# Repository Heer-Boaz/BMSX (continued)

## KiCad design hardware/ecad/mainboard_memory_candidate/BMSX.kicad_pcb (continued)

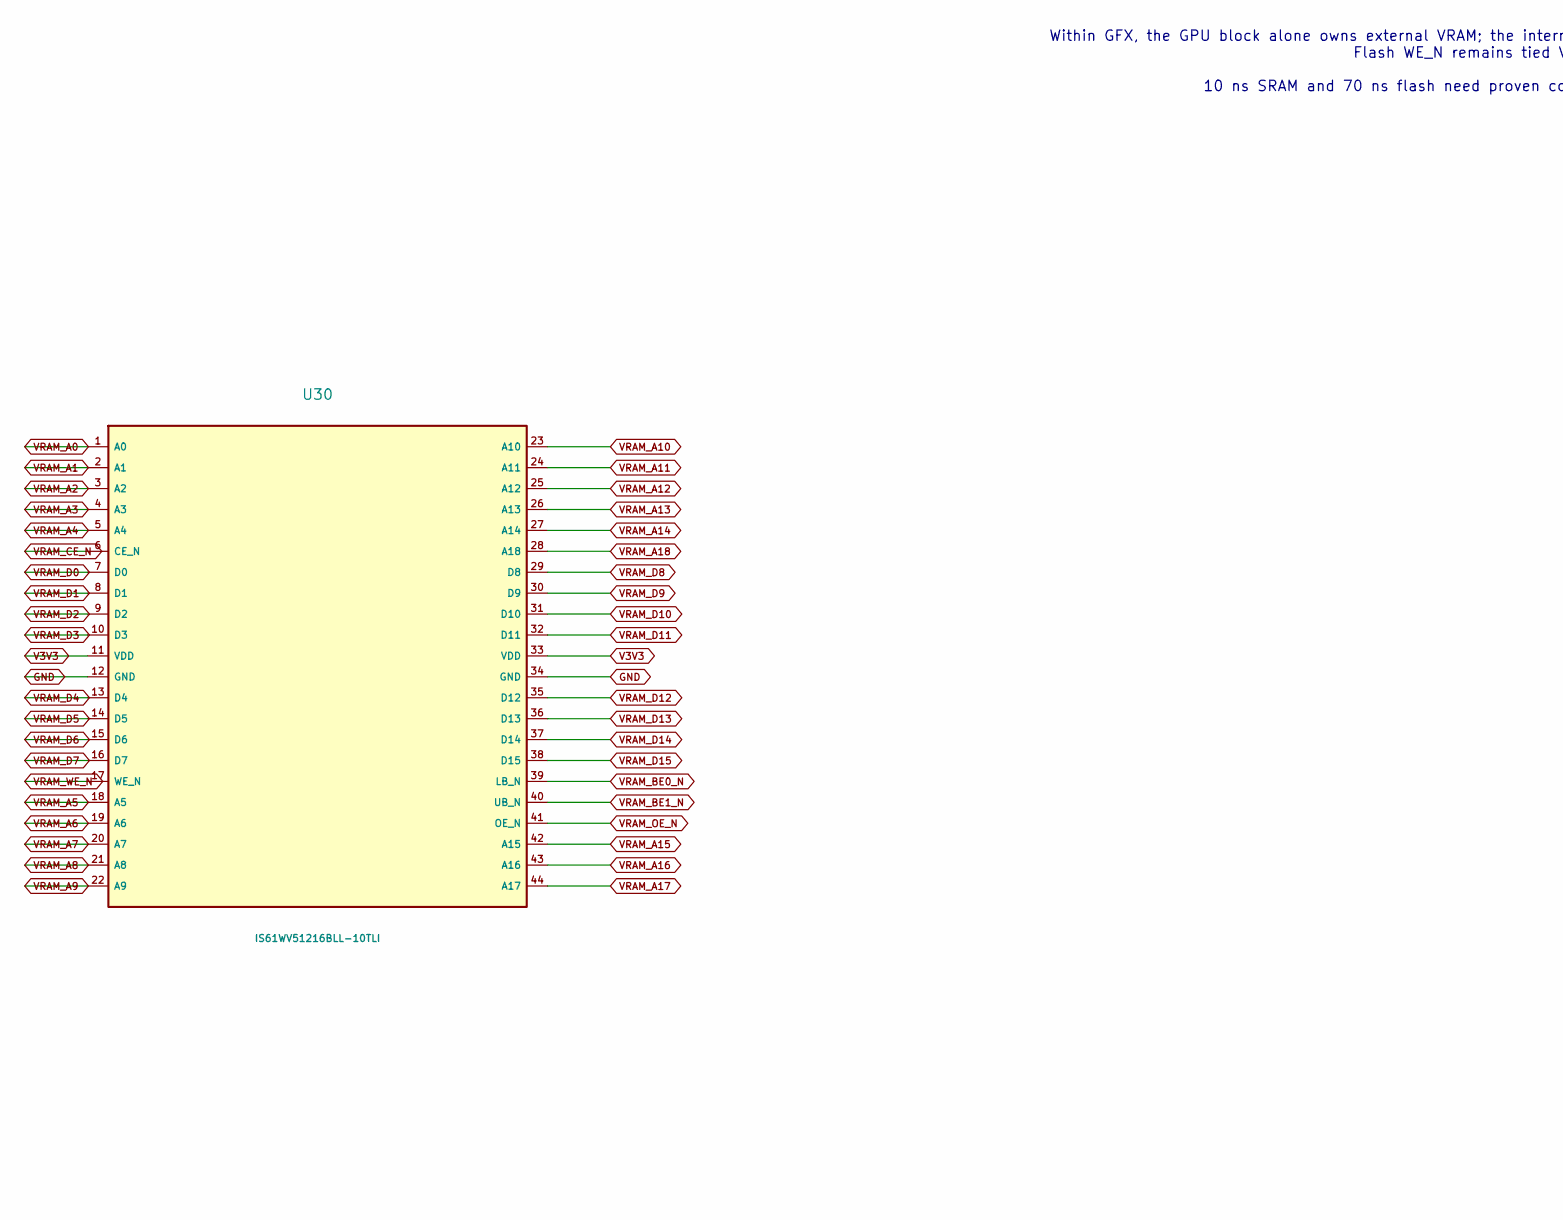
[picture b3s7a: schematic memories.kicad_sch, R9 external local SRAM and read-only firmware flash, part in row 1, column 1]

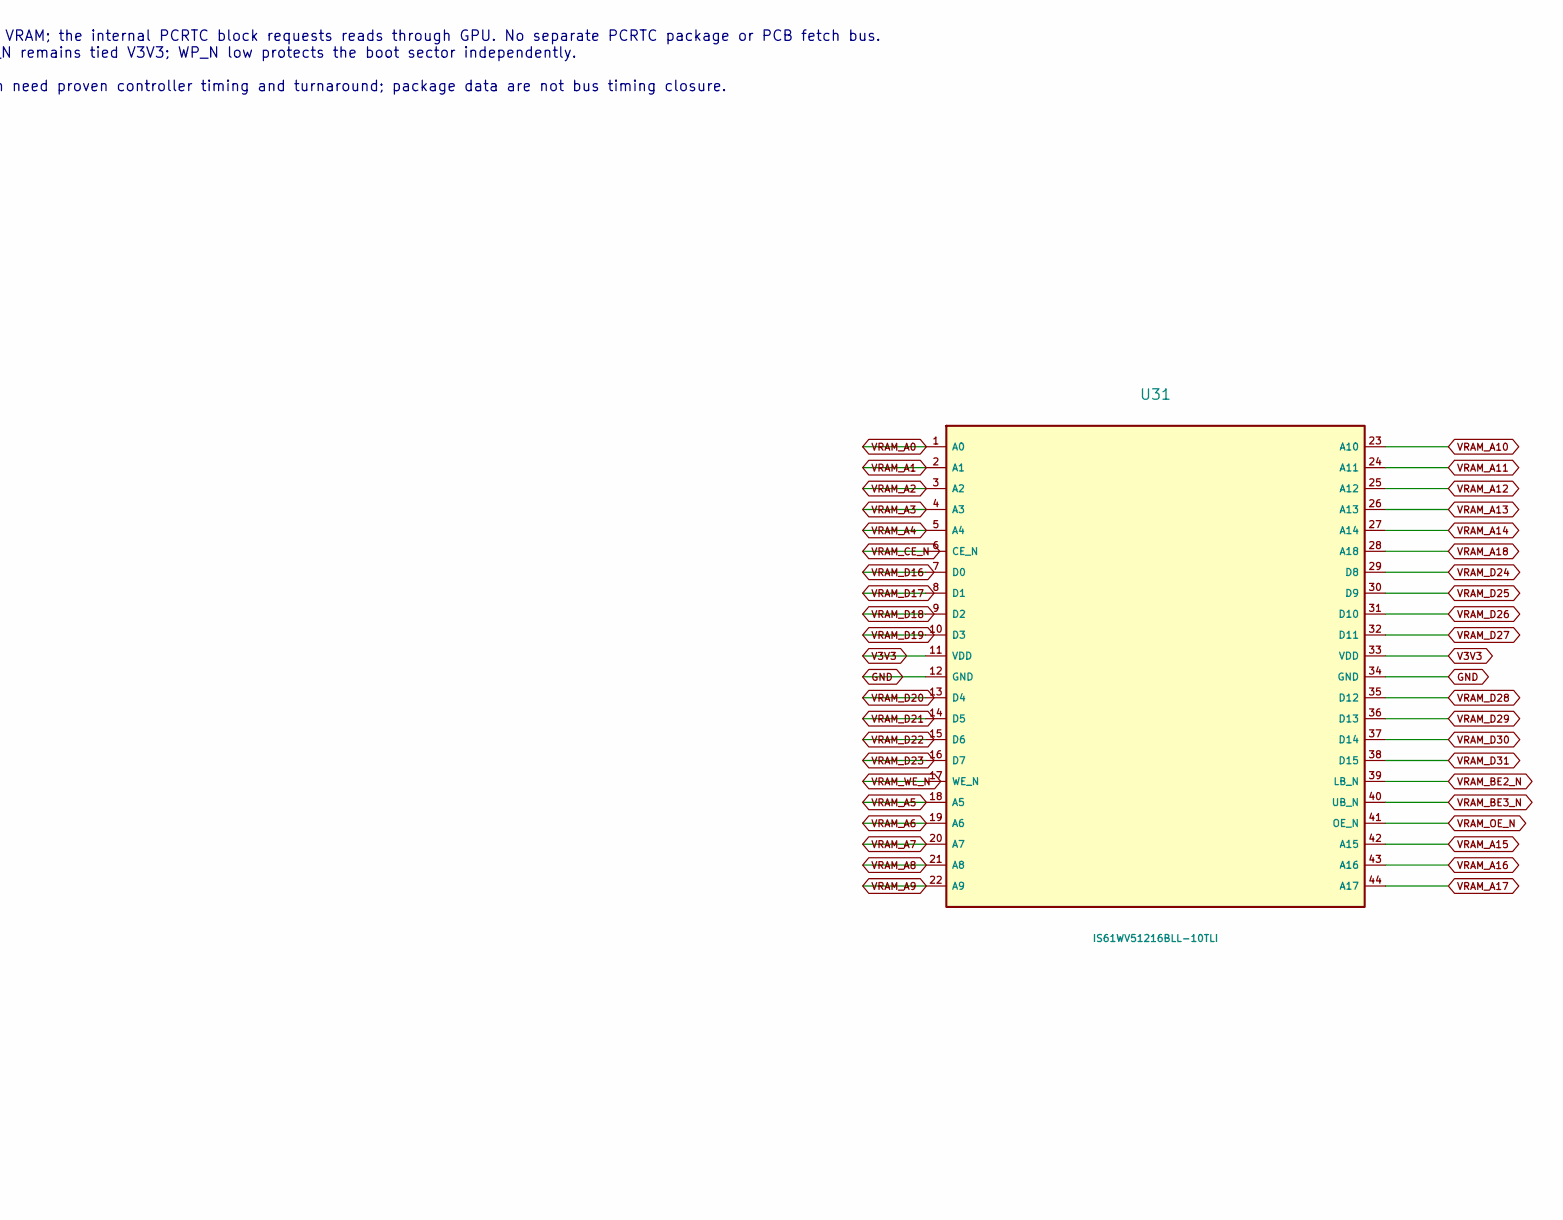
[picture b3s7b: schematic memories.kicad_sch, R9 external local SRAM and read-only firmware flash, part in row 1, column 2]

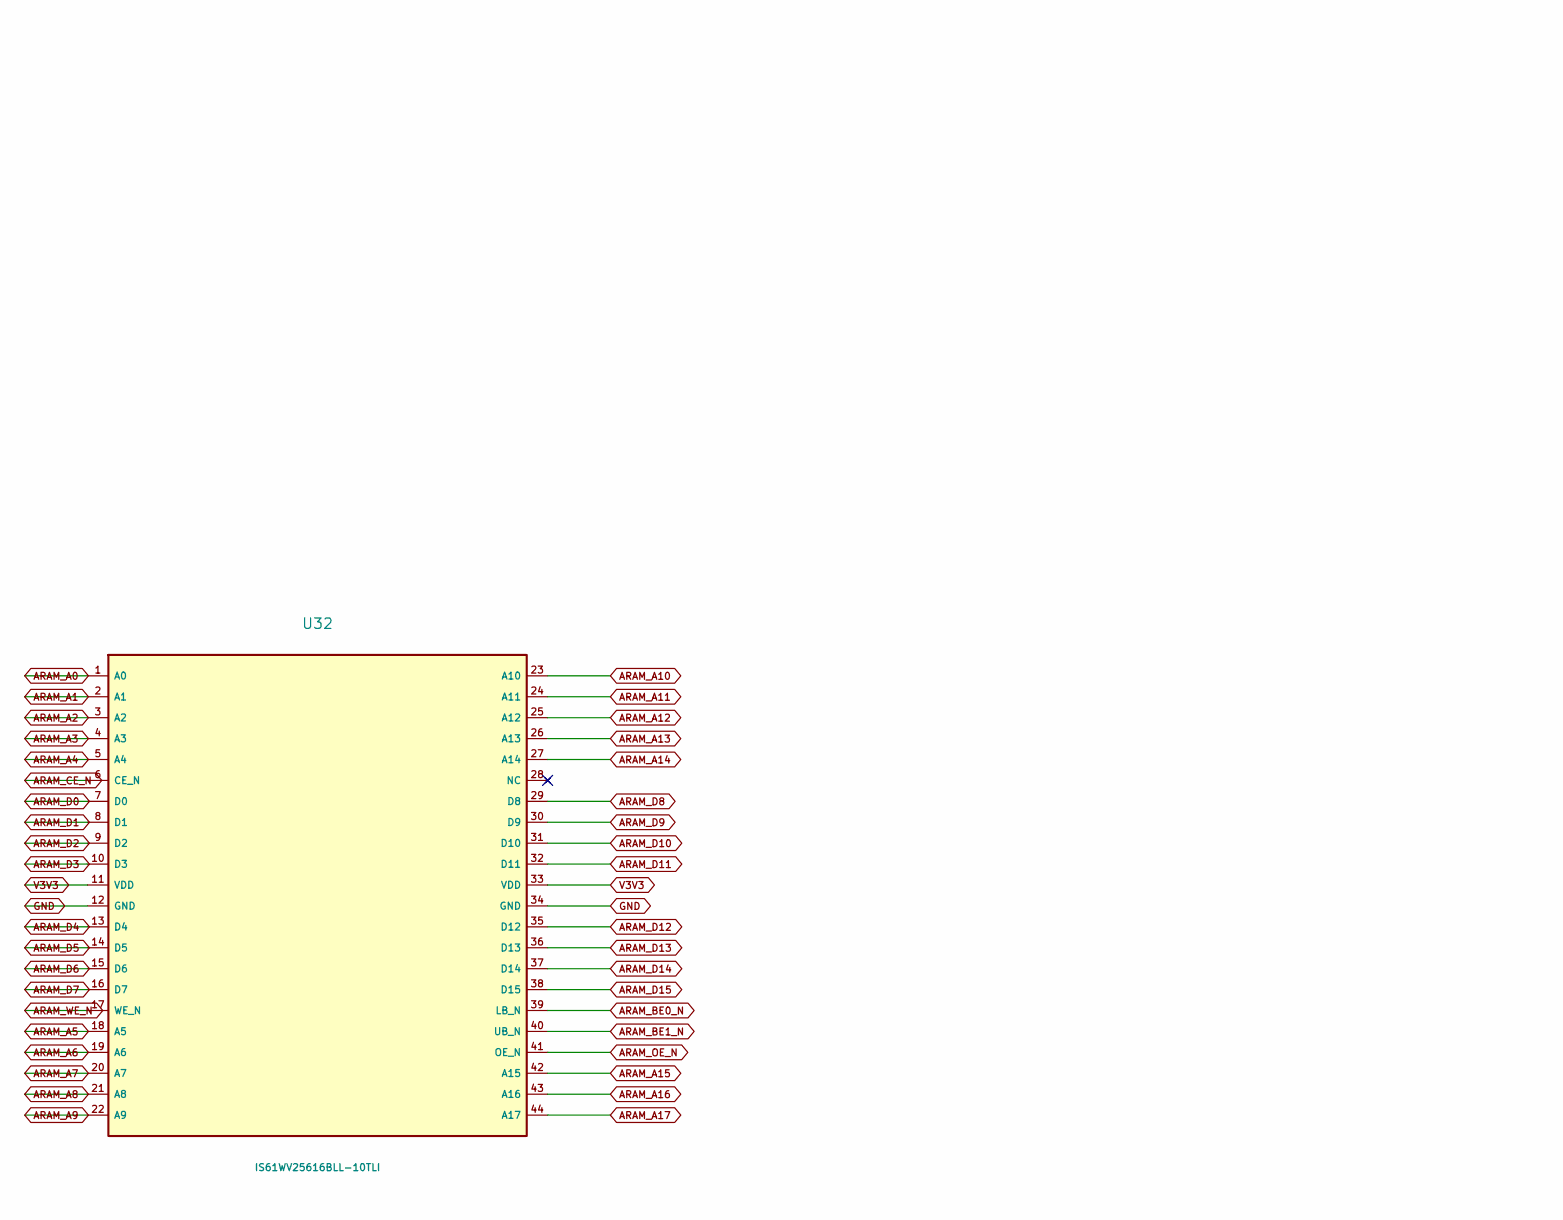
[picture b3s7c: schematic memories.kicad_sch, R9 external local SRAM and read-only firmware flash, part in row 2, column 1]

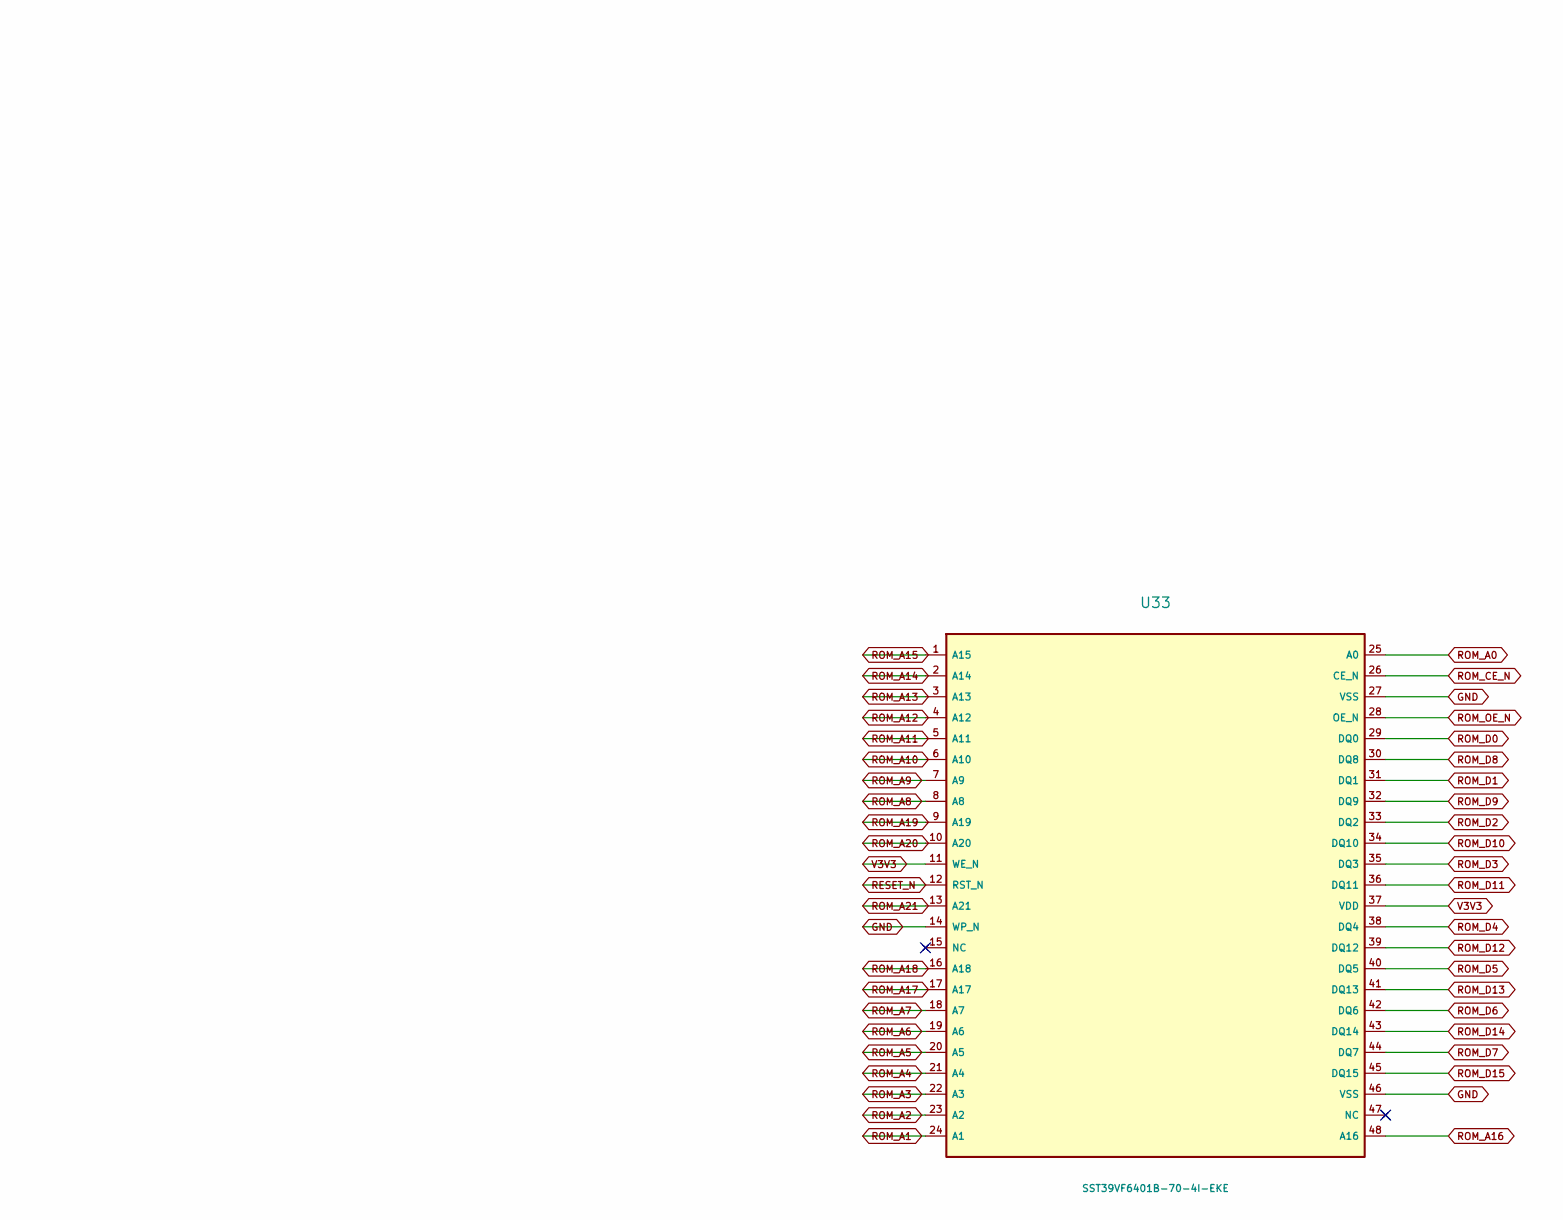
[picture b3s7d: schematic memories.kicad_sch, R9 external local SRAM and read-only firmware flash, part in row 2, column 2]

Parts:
U30: IS61WV51216BLL-10TLI; U30
U31: IS61WV51216BLL-10TLI; U31
U32: IS61WV25616BLL-10TLI; U32
U33: SST39VF6401B-70-4I-EKE; U33

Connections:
ARAM_A0: U32.1 (A0); also elsewhere on the board
ARAM_A1: U32.2 (A1); also elsewhere on the board
ARAM_A2: U32.3 (A2); also elsewhere on the board
ARAM_A3: U32.4 (A3); also elsewhere on the board
ARAM_A4: U32.5 (A4); also elsewhere on the board
ARAM_A5: U32.18 (A5); also elsewhere on the board
ARAM_A6: U32.19 (A6); also elsewhere on the board
ARAM_A7: U32.20 (A7); also elsewhere on the board
ARAM_A8: U32.21 (A8); also elsewhere on the board
ARAM_A9: U32.22 (A9); also elsewhere on the board
ARAM_A10: U32.23 (A10); also elsewhere on the board
ARAM_A11: U32.24 (A11); also elsewhere on the board
ARAM_A12: U32.25 (A12); also elsewhere on the board
ARAM_A13: U32.26 (A13); also elsewhere on the board
ARAM_A14: U32.27 (A14); also elsewhere on the board
ARAM_A15: U32.42 (A15); also elsewhere on the board
ARAM_A16: U32.43 (A16); also elsewhere on the board
ARAM_A17: U32.44 (A17); also elsewhere on the board
ARAM_BE0_N: U32.39 (LB_N); also elsewhere on the board
ARAM_BE1_N: U32.40 (UB_N); also elsewhere on the board
ARAM_CE_N: U32.6 (CE_N); also elsewhere on the board
ARAM_D0: U32.7 (D0); also elsewhere on the board
ARAM_D1: U32.8 (D1); also elsewhere on the board
ARAM_D2: U32.9 (D2); also elsewhere on the board
ARAM_D3: U32.10 (D3); also elsewhere on the board
ARAM_D4: U32.13 (D4); also elsewhere on the board
ARAM_D5: U32.14 (D5); also elsewhere on the board
ARAM_D6: U32.15 (D6); also elsewhere on the board
ARAM_D7: U32.16 (D7); also elsewhere on the board
ARAM_D8: U32.29 (D8); also elsewhere on the board
ARAM_D9: U32.30 (D9); also elsewhere on the board
ARAM_D10: U32.31 (D10); also elsewhere on the board
ARAM_D11: U32.32 (D11); also elsewhere on the board
ARAM_D12: U32.35 (D12); also elsewhere on the board
ARAM_D13: U32.36 (D13); also elsewhere on the board
ARAM_D14: U32.37 (D14); also elsewhere on the board
ARAM_D15: U32.38 (D15); also elsewhere on the board
ARAM_OE_N: U32.41 (OE_N); also elsewhere on the board
ARAM_WE_N: U32.17 (WE_N); also elsewhere on the board
GND: U30.12 (GND), U30.34 (GND), U31.12 (GND), U31.34 (GND), U32.12 (GND), U32.34 (GND), U33.14 (WP_N), U33.27 (VSS), U33.46 (VSS); also elsewhere on the board
RESET_N: U33.12 (RST_N); also elsewhere on the board
ROM_A0: U33.25 (A0); also elsewhere on the board
ROM_A1: U33.24 (A1); also elsewhere on the board
ROM_A2: U33.23 (A2); also elsewhere on the board
ROM_A3: U33.22 (A3); also elsewhere on the board
ROM_A4: U33.21 (A4); also elsewhere on the board
ROM_A5: U33.20 (A5); also elsewhere on the board
ROM_A6: U33.19 (A6); also elsewhere on the board
ROM_A7: U33.18 (A7); also elsewhere on the board
ROM_A8: U33.8 (A8); also elsewhere on the board
ROM_A9: U33.7 (A9); also elsewhere on the board
ROM_A10: U33.6 (A10); also elsewhere on the board
ROM_A11: U33.5 (A11); also elsewhere on the board
ROM_A12: U33.4 (A12); also elsewhere on the board
ROM_A13: U33.3 (A13); also elsewhere on the board
ROM_A14: U33.2 (A14); also elsewhere on the board
ROM_A15: U33.1 (A15); also elsewhere on the board
ROM_A16: U33.48 (A16); also elsewhere on the board
ROM_A17: U33.17 (A17); also elsewhere on the board
ROM_A18: U33.16 (A18); also elsewhere on the board
ROM_A19: U33.9 (A19); also elsewhere on the board
ROM_A20: U33.10 (A20); also elsewhere on the board
ROM_A21: U33.13 (A21); also elsewhere on the board
ROM_CE_N: U33.26 (CE_N); also elsewhere on the board
ROM_D0: U33.29 (DQ0); also elsewhere on the board
ROM_D1: U33.31 (DQ1); also elsewhere on the board
ROM_D2: U33.33 (DQ2); also elsewhere on the board
ROM_D3: U33.35 (DQ3); also elsewhere on the board
ROM_D4: U33.38 (DQ4); also elsewhere on the board
ROM_D5: U33.40 (DQ5); also elsewhere on the board
ROM_D6: U33.42 (DQ6); also elsewhere on the board
ROM_D7: U33.44 (DQ7); also elsewhere on the board
ROM_D8: U33.30 (DQ8); also elsewhere on the board
ROM_D9: U33.32 (DQ9); also elsewhere on the board
ROM_D10: U33.34 (DQ10); also elsewhere on the board
ROM_D11: U33.36 (DQ11); also elsewhere on the board
ROM_D12: U33.39 (DQ12); also elsewhere on the board
ROM_D13: U33.41 (DQ13); also elsewhere on the board
ROM_D14: U33.43 (DQ14); also elsewhere on the board
ROM_D15: U33.45 (DQ15); also elsewhere on the board
ROM_OE_N: U33.28 (OE_N); also elsewhere on the board
V3V3: U30.11 (VDD), U30.33 (VDD), U31.11 (VDD), U31.33 (VDD), U32.11 (VDD), U32.33 (VDD), U33.11 (WE_N), U33.37 (VDD); also elsewhere on the board
VRAM_A0: U30.1 (A0), U31.1 (A0); also elsewhere on the board
VRAM_A1: U30.2 (A1), U31.2 (A1); also elsewhere on the board
VRAM_A2: U30.3 (A2), U31.3 (A2); also elsewhere on the board
VRAM_A3: U30.4 (A3), U31.4 (A3); also elsewhere on the board
VRAM_A4: U30.5 (A4), U31.5 (A4); also elsewhere on the board
VRAM_A5: U30.18 (A5), U31.18 (A5); also elsewhere on the board
VRAM_A6: U30.19 (A6), U31.19 (A6); also elsewhere on the board
VRAM_A7: U30.20 (A7), U31.20 (A7); also elsewhere on the board
VRAM_A8: U30.21 (A8), U31.21 (A8); also elsewhere on the board
VRAM_A9: U30.22 (A9), U31.22 (A9); also elsewhere on the board
VRAM_A10: U30.23 (A10), U31.23 (A10); also elsewhere on the board
VRAM_A11: U30.24 (A11), U31.24 (A11); also elsewhere on the board
VRAM_A12: U30.25 (A12), U31.25 (A12); also elsewhere on the board
VRAM_A13: U30.26 (A13), U31.26 (A13); also elsewhere on the board
VRAM_A14: U30.27 (A14), U31.27 (A14); also elsewhere on the board
VRAM_A15: U30.42 (A15), U31.42 (A15); also elsewhere on the board
VRAM_A16: U30.43 (A16), U31.43 (A16); also elsewhere on the board
VRAM_A17: U30.44 (A17), U31.44 (A17); also elsewhere on the board
VRAM_A18: U30.28 (A18), U31.28 (A18); also elsewhere on the board
VRAM_BE0_N: U30.39 (LB_N); also elsewhere on the board
VRAM_BE1_N: U30.40 (UB_N); also elsewhere on the board
VRAM_BE2_N: U31.39 (LB_N); also elsewhere on the board
VRAM_BE3_N: U31.40 (UB_N); also elsewhere on the board
VRAM_CE_N: U30.6 (CE_N), U31.6 (CE_N); also elsewhere on the board
VRAM_D0: U30.7 (D0); also elsewhere on the board
VRAM_D1: U30.8 (D1); also elsewhere on the board
VRAM_D2: U30.9 (D2); also elsewhere on the board
VRAM_D3: U30.10 (D3); also elsewhere on the board
VRAM_D4: U30.13 (D4); also elsewhere on the board
VRAM_D5: U30.14 (D5); also elsewhere on the board
VRAM_D6: U30.15 (D6); also elsewhere on the board
VRAM_D7: U30.16 (D7); also elsewhere on the board
VRAM_D8: U30.29 (D8); also elsewhere on the board
VRAM_D9: U30.30 (D9); also elsewhere on the board
VRAM_D10: U30.31 (D10); also elsewhere on the board
VRAM_D11: U30.32 (D11); also elsewhere on the board
VRAM_D12: U30.35 (D12); also elsewhere on the board
VRAM_D13: U30.36 (D13); also elsewhere on the board
VRAM_D14: U30.37 (D14); also elsewhere on the board
VRAM_D15: U30.38 (D15); also elsewhere on the board
VRAM_D16: U31.7 (D0); also elsewhere on the board
VRAM_D17: U31.8 (D1); also elsewhere on the board
VRAM_D18: U31.9 (D2); also elsewhere on the board
VRAM_D19: U31.10 (D3); also elsewhere on the board
VRAM_D20: U31.13 (D4); also elsewhere on the board
VRAM_D21: U31.14 (D5); also elsewhere on the board
VRAM_D22: U31.15 (D6); also elsewhere on the board
VRAM_D23: U31.16 (D7); also elsewhere on the board
VRAM_D24: U31.29 (D8); also elsewhere on the board
VRAM_D25: U31.30 (D9); also elsewhere on the board
VRAM_D26: U31.31 (D10); also elsewhere on the board
VRAM_D27: U31.32 (D11); also elsewhere on the board
VRAM_D28: U31.35 (D12); also elsewhere on the board
VRAM_D29: U31.36 (D13); also elsewhere on the board
VRAM_D30: U31.37 (D14); also elsewhere on the board
VRAM_D31: U31.38 (D15); also elsewhere on the board
VRAM_OE_N: U30.41 (OE_N), U31.41 (OE_N); also elsewhere on the board
VRAM_WE_N: U30.17 (WE_N), U31.17 (WE_N); also elsewhere on the board

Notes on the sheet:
Within GFX, the GPU block alone owns external VRAM; the internal PCRTC block requests reads through GPU. No separate PCRTC package or PCB fetch bus. Flash WE_N remains tied V3V3; WP_N low protects the boot sector independently.
10 ns SRAM and 70 ns flash need proven controller timing and turnaround; package data are not bus timing closure.

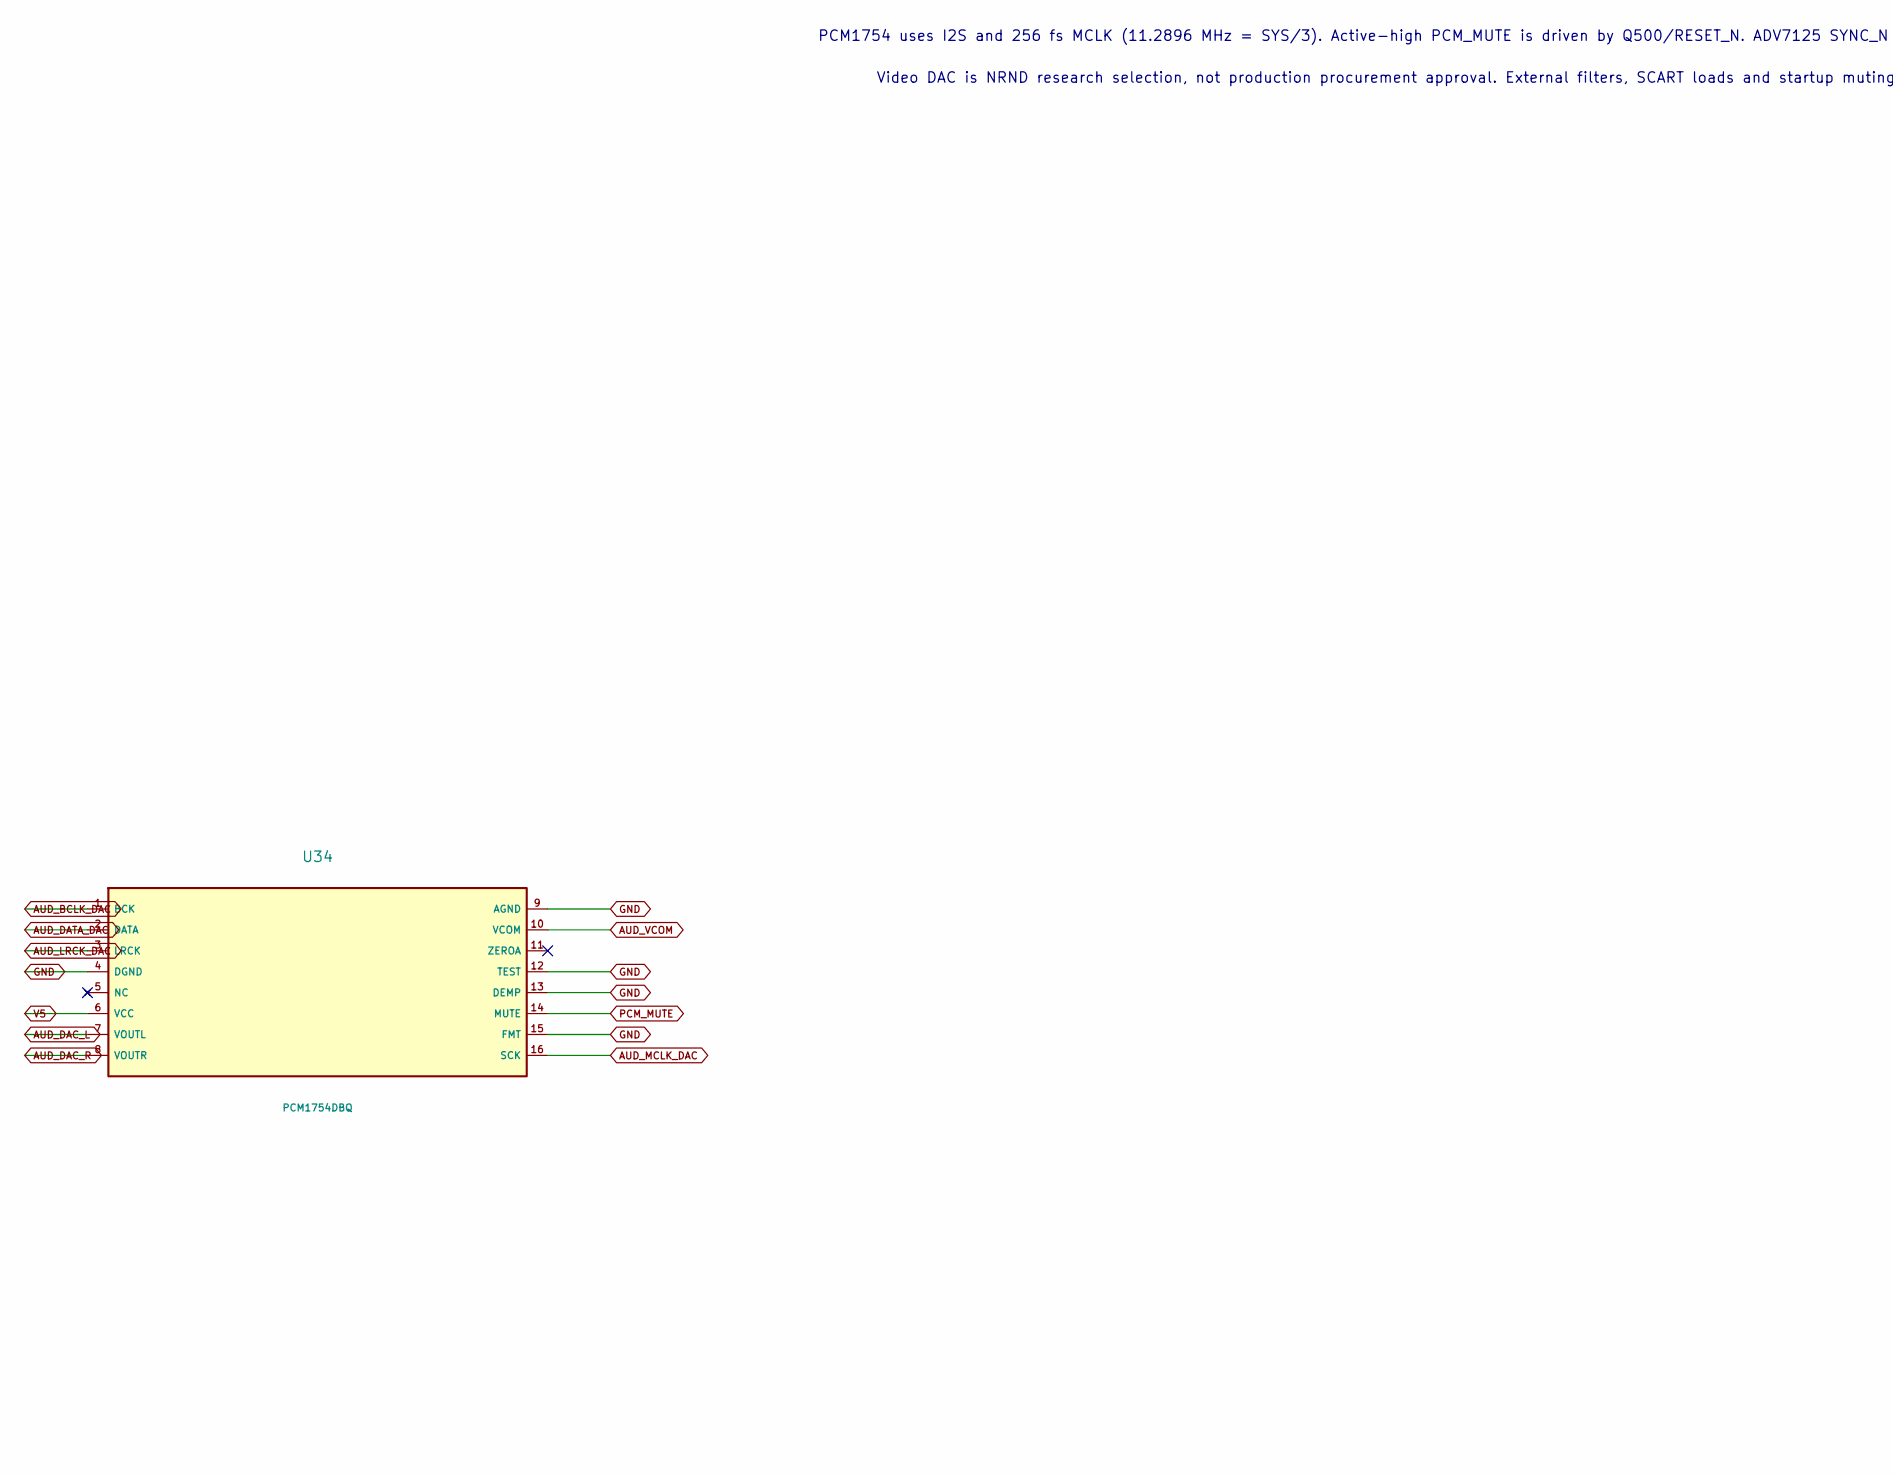
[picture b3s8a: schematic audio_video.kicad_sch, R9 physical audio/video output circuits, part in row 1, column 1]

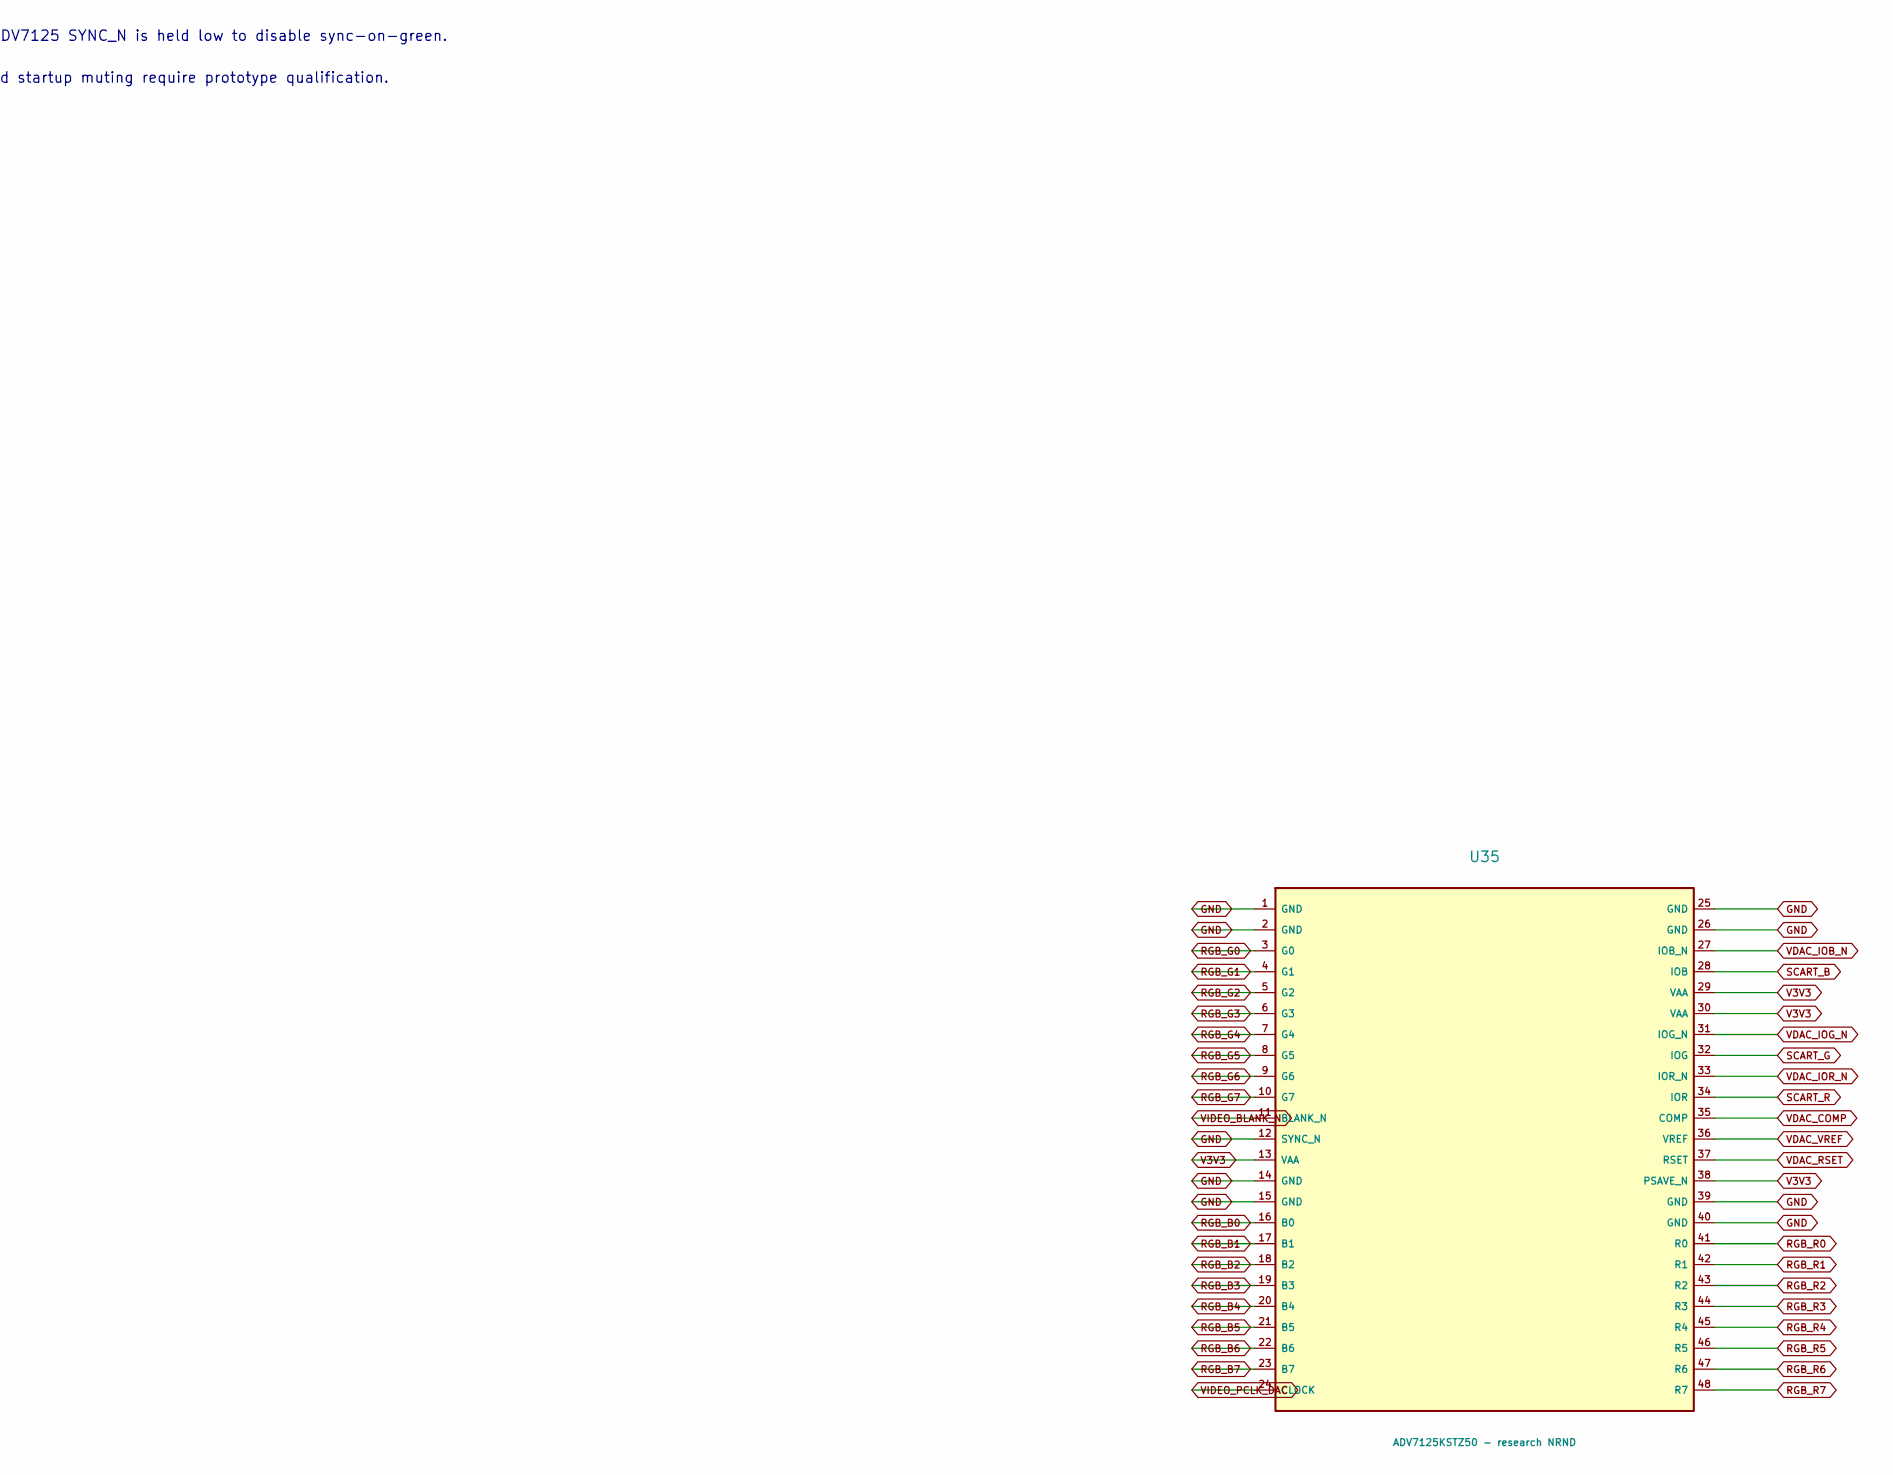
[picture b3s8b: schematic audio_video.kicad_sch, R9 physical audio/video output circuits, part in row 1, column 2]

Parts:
U34: PCM1754DBQ; U34
U35: ADV7125KSTZ50 - research NRND; U35

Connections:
AUD_BCLK_DAC: U34.1 (BCK); also elsewhere on the board
AUD_DAC_L: U34.7 (VOUTL); also elsewhere on the board
AUD_DAC_R: U34.8 (VOUTR); also elsewhere on the board
AUD_DATA_DAC: U34.2 (DATA); also elsewhere on the board
AUD_LRCK_DAC: U34.3 (LRCK); also elsewhere on the board
AUD_MCLK_DAC: U34.16 (SCK); also elsewhere on the board
AUD_VCOM: U34.10 (VCOM); also elsewhere on the board
GND: U34.4 (DGND), U34.9 (AGND), U34.12 (TEST), U34.13 (DEMP), U34.15 (FMT), U35.1 (GND), U35.2 (GND), U35.12 (SYNC_N), U35.14 (GND), U35.15 (GND), U35.25 (GND), U35.26 (GND), U35.39 (GND), U35.40 (GND); also elsewhere on the board
PCM_MUTE: U34.14 (MUTE); also elsewhere on the board
RGB_B0: U35.16 (B0); also elsewhere on the board
RGB_B1: U35.17 (B1); also elsewhere on the board
RGB_B2: U35.18 (B2); also elsewhere on the board
RGB_B3: U35.19 (B3); also elsewhere on the board
RGB_B4: U35.20 (B4); also elsewhere on the board
RGB_B5: U35.21 (B5); also elsewhere on the board
RGB_B6: U35.22 (B6); also elsewhere on the board
RGB_B7: U35.23 (B7); also elsewhere on the board
RGB_G0: U35.3 (G0); also elsewhere on the board
RGB_G1: U35.4 (G1); also elsewhere on the board
RGB_G2: U35.5 (G2); also elsewhere on the board
RGB_G3: U35.6 (G3); also elsewhere on the board
RGB_G4: U35.7 (G4); also elsewhere on the board
RGB_G5: U35.8 (G5); also elsewhere on the board
RGB_G6: U35.9 (G6); also elsewhere on the board
RGB_G7: U35.10 (G7); also elsewhere on the board
RGB_R0: U35.41 (R0); also elsewhere on the board
RGB_R1: U35.42 (R1); also elsewhere on the board
RGB_R2: U35.43 (R2); also elsewhere on the board
RGB_R3: U35.44 (R3); also elsewhere on the board
RGB_R4: U35.45 (R4); also elsewhere on the board
RGB_R5: U35.46 (R5); also elsewhere on the board
RGB_R6: U35.47 (R6); also elsewhere on the board
RGB_R7: U35.48 (R7); also elsewhere on the board
SCART_B: U35.28 (IOB); also elsewhere on the board
SCART_G: U35.32 (IOG); also elsewhere on the board
SCART_R: U35.34 (IOR); also elsewhere on the board
V3V3: U35.13 (VAA), U35.29 (VAA), U35.30 (VAA), U35.38 (PSAVE_N); also elsewhere on the board
V5: U34.6 (VCC); also elsewhere on the board
VDAC_COMP: U35.35 (COMP); also elsewhere on the board
VDAC_IOB_N: U35.27 (IOB_N); also elsewhere on the board
VDAC_IOG_N: U35.31 (IOG_N); also elsewhere on the board
VDAC_IOR_N: U35.33 (IOR_N); also elsewhere on the board
VDAC_RSET: U35.37 (RSET); also elsewhere on the board
VDAC_VREF: U35.36 (VREF); also elsewhere on the board
VIDEO_BLANK_N: U35.11 (BLANK_N); also elsewhere on the board
VIDEO_PCLK_DAC: U35.24 (CLOCK); also elsewhere on the board

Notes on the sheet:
PCM1754 uses I2S and 256 fs MCLK (11.2896 MHz = SYS/3). Active-high PCM_MUTE is driven by Q500/RESET_N. ADV7125 SYNC_N is held low to disable sync-on-green.
Video DAC is NRND research selection, not production procurement approval. External filters, SCART loads and startup muting require prototype qualification.

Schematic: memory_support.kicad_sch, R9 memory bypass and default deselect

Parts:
C500: 100nF 16V X7R; C500
C501: 100nF 16V X7R; C501
C502: 1uF 16V X7R; C502
C503: 100nF 16V X7R; C503
C504: 100nF 16V X7R; C504
C505: 1uF 16V X7R; C505
C506: 100nF 16V X7R; C506
C507: 100nF 16V X7R; C507
C508: 1uF 16V X7R; C508
C509: 100nF 16V X7R; C509
C510: 1uF 16V X7R; C510
R500: 10k 1%; R500
R501: 10k 1%; R501
R502: 10k 1%; R502
R503: 10k 1%; R503
R504: 10k 1%; R504
R505: 10k 1%; R505
R506: 10k 1%; R506
R507: 10k 1%; R507

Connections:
ARAM_CE_N: R503.1; also elsewhere on the board
ARAM_OE_N: R504.1; also elsewhere on the board
ARAM_WE_N: R505.1; also elsewhere on the board
GND: C500.2, C501.2, C502.2, C503.2, C504.2, C505.2, C506.2, C507.2, C508.2, C509.2, C510.2; also elsewhere on the board
ROM_CE_N: R506.1; also elsewhere on the board
ROM_OE_N: R507.1; also elsewhere on the board
V3V3: C500.1, C501.1, C502.1, C503.1, C504.1, C505.1, C506.1, C507.1, C508.1, C509.1, C510.1, R500.2, R501.2, R502.2, R503.2, R504.2, R505.2, R506.2, R507.2; also elsewhere on the board
VRAM_CE_N: R500.1; also elsewhere on the board
VRAM_OE_N: R501.1; also elsewhere on the board
VRAM_WE_N: R502.1; also elsewhere on the board

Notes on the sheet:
Local 100nF at every VDD pair; 1uF per SRAM. Pull-ups inhibit memory while proposed ASIC pads are Hi-Z.

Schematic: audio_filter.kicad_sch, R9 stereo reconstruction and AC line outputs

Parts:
C525: 100nF 16V X7R; C525
C526: 1uF 16V X7R; C526
C527: 1n0 1% C0G 25V; C527
C528: 470pF 1% C0G 25V; C528
C529: 10uF 16V aluminum; C529
C530: 1n0 1% C0G 25V; C530
C531: 470pF 1% C0G 25V; C531
C532: 10uF 16V aluminum; C532
R517: 6k8 1%; R517
R518: 6k8 1%; R518
R519: 2k2 1%; R519
R520: 1k2 1%; R520
R521: 6k8 1%; R521
R522: 6k8 1%; R522
R523: 2k2 1%; R523
R524: 1k2 1%; R524
U41: OPA2353UA; U41

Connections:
AUD_AC_L: C529.2, R519.1
AUD_AC_R: C532.2, R523.1
AUD_DAC_L: R517.1; also elsewhere on the board
AUD_DAC_R: R521.1; also elsewhere on the board
AUD_FILTER_L: C527.2, C529.1, U41.1 (OUT_A), U41.2 (IN-_A)
AUD_FILTER_R: C530.2, C532.1, U41.6 (IN-_B), U41.7 (OUT_B)
AUD_SK1_L: C527.1, R517.2, R518.1
AUD_SK1_R: C530.1, R521.2, R522.1
AUD_SK2_L: C528.1, R518.2, U41.3 (IN+_A)
AUD_SK2_R: C531.1, R522.2, U41.5 (IN+_B)
GND: C525.2, C526.2, C528.2, C531.2, R520.2, R524.2, U41.4 (V-); also elsewhere on the board
SCART_AUD_L: R519.2, R520.1; also elsewhere on the board
SCART_AUD_R: R523.2, R524.1; also elsewhere on the board
V5: C525.1, C526.1, U41.8 (V+); also elsewhere on the board

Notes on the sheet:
Unity-gain Sallen-Key proposal: R1=R2=6k8, C1=1n0, C2=470pF; f0=34.1kHz, Q=0.729 ideal. Not a measured THD/noise result.
10uF output coupling and 2k2/1k2 divider: about0.463Vrms at fullscale into10kOhm. No headphone or loudspeaker output.

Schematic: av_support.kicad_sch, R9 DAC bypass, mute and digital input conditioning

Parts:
C511: 100nF 16V X7R; C511
C512: 10uF 16V aluminum; C512; MPN UWT1C100MCL1GB
C513: 10uF 16V aluminum; C513; MPN UWT1C100MCL1GB
C514: 100nF 16V X7R; C514
C515: 100nF 16V X7R; C515
C516: 100nF 16V X7R; C516
C517: 10nF 16V X7R; C517
C518: 100nF 16V X7R; C518
C519: 10nF 16V X7R; C519
C520: 100nF 16V X7R; C520
C521: 10nF 16V X7R; C521
C522: 1uF 16V X7R; C522
C523: 100nF 16V X7R; C523
C524: 100nF 16V X7R; C524
Q500: BSS138; Q500
R508: 33R 1%; R508
R509: 33R 1%; R509
R510: 33R 1%; R510
R511: 33R 1%; R511
R512: 10k 1%; R512
R513: 100k 1%; R513
R514: 10k 1%; R514
R515: 33R 1%; R515
R516: 536R 0.1%; R516
U40: SN74LVC1G125DBVR; U40
U42: SN74LVC1G125DBVR; U42

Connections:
AUD_BCLK: R509.1; also elsewhere on the board
AUD_BCLK_DAC: R509.2; also elsewhere on the board
AUD_DATA: R511.1; also elsewhere on the board
AUD_DATA_DAC: R511.2; also elsewhere on the board
AUD_LRCK: R510.1; also elsewhere on the board
AUD_LRCK_DAC: R510.2; also elsewhere on the board
AUD_MCLK: R508.1; also elsewhere on the board
AUD_MCLK_DAC: R508.2; also elsewhere on the board
AUD_VCOM: C513.1; also elsewhere on the board
GND: C511.2, C512.2, C513.2, C514.2, C515.2, C516.2, C517.2, C518.2, C519.2, C520.2, C521.2, C522.2, C524.2, Q500.2 (S), R513.2, R514.2, R516.2, U40.1 (OE_N), U40.3 (GND), U42.1 (OE_N), U42.3 (GND); also elsewhere on the board
PCM_MUTE: Q500.3 (D), R512.1; also elsewhere on the board
RESET_N: Q500.1 (G), R513.1; also elsewhere on the board
V3V3: C514.1, C515.1, C516.1, C517.1, C518.1, C519.1, C520.1, C521.1, C522.1, C523.2, U40.5 (VCC), U42.5 (VCC); also elsewhere on the board
V5: C511.1, C512.1, R512.2; also elsewhere on the board
VDAC_COMP: C523.1; also elsewhere on the board
VDAC_RSET: R516.1; also elsewhere on the board
VDAC_VREF: C524.1; also elsewhere on the board
VIDEO_BLANK_N: R514.1; also elsewhere on the board
VIDEO_CSYNC_BUF: U42.4 (Y); also elsewhere on the board
VIDEO_CSYNC_N: U42.2 (A); also elsewhere on the board
VIDEO_PCLK: U40.2 (A); also elsewhere on the board
VIDEO_PCLK_BUF: R515.1, U40.4 (Y)
VIDEO_PCLK_DAC: R515.2; also elsewhere on the board

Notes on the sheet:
PCM1754 active-high PCM_MUTE is default-pulled to V5. Q500 BSS138 pulls it low only when RESET_N is high; no V5 pull-up on 3V3 logic.
SN74LVC1G125 supplies dedicated video clock drive and a separate sync line driver. Buffer delay and RGB setup/hold remain timing closure obligations.
